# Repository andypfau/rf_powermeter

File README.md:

RF Powermeter
=============

A 10 MHz to 8 GHz RF power meter with USB connectivity.

## Design

## Photos

## Project Status

The hardware is working. The firmware is considered beta, but all functionality is implemented, and should work.

### Thoughts on Design

- The SMA connector is quite cheap, and will probably not last long (no stainless steel). Also, with the current design, the SMA tighening torque might break the solder connectio to the PCB (happened during testing).
- The HMC602 is EOL (see production notes below).

## Further Reading

- [RF Design](./doc/rfdesign.md)
- [Design Tools](./doc/designtools.md)
- [Production](./doc/production.md)
- [Serial Interface](./doc/serial.md)
- [Measurements](./doc/measurements.md)
- [Hardware Revisions](./doc/hwrev.md)

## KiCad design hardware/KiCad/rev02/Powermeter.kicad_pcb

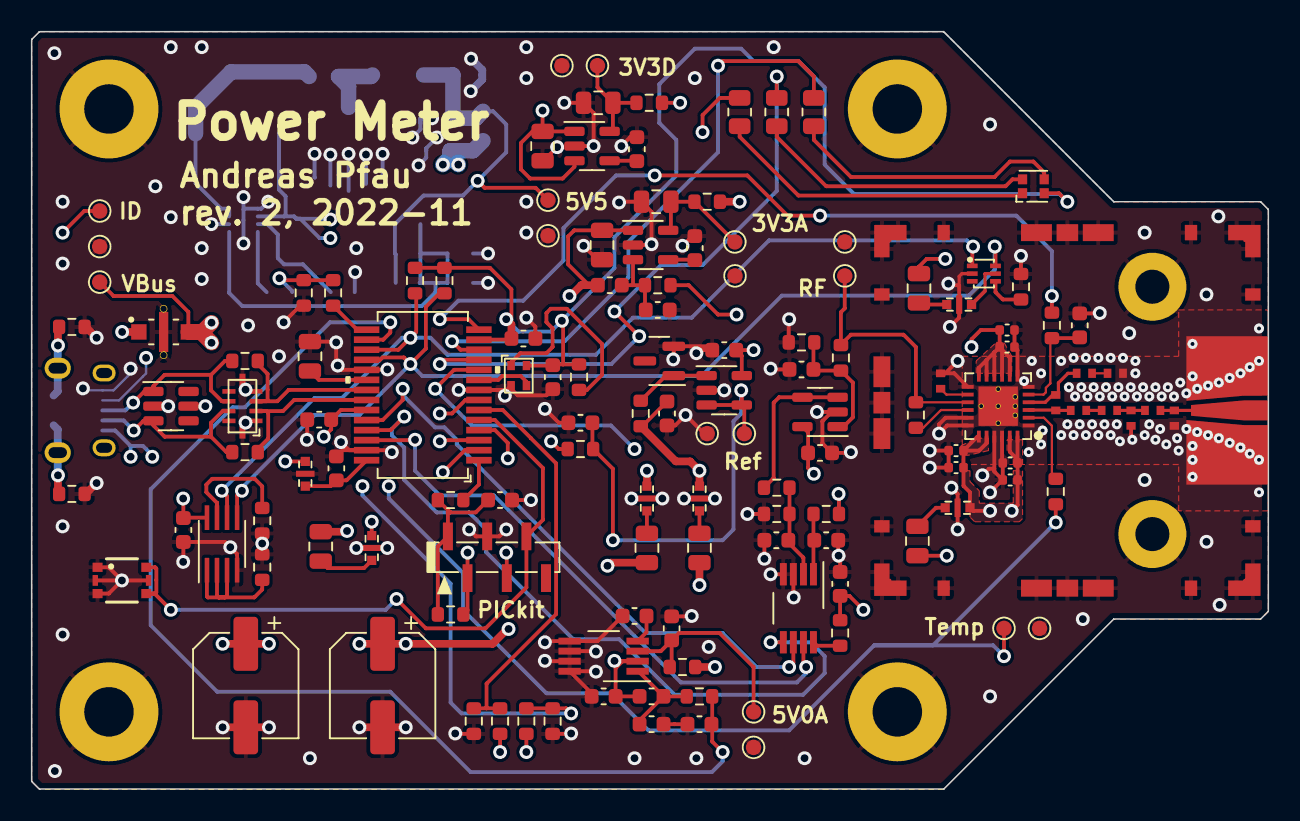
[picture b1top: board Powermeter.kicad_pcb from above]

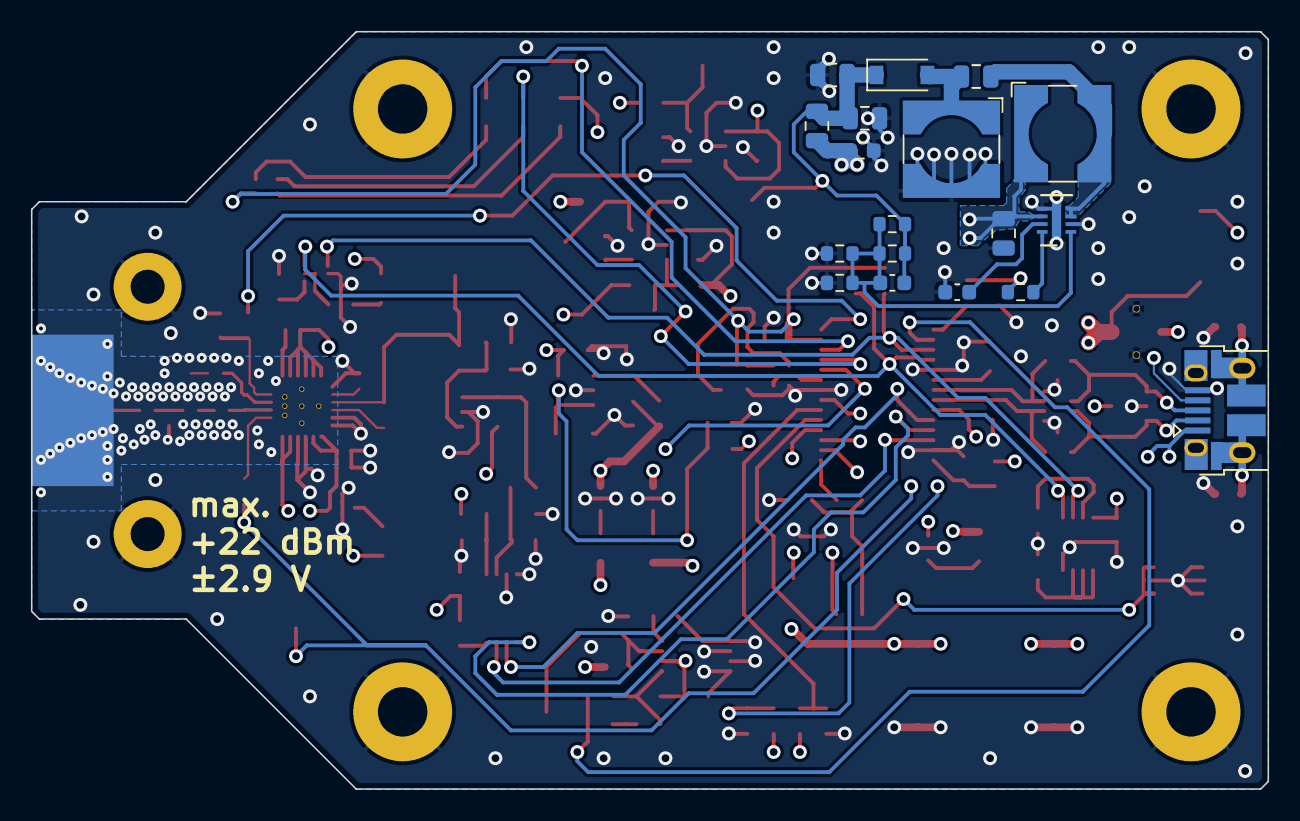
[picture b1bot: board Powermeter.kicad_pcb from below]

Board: 4 copper layers, 80.0 x 49.0 mm, 162 parts (18 on the bottom side), 84 nets.

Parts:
C301, C304, C306, C307, C308, C309, C402, C404, C410, C413, C602, C604, C605, C608, C609: C_100n_25V_Z5U_0603_small; C_0603_1608Metric
C302, C305, C501, C502, C601, C606: C_FT_100n_16V_0603; C_Feedthru_0603
C303, C416, C418: C_10n_50V_X7R_0603_small; C_0603_1608Metric
C310, C401, C411, C412, C417, C419: C_10µ_25V_X7R_0805; C_0805_2012Metric
C403: C_47n_50V_Z5U_0603_small; C_0603_1608Metric
C405, C407: C_Al_330µ_16V_UUD1C330MCL1GS; CP_Elec_6.3x5.8
C406, C414, C415: C_1µ_25V_X7R_0805; C_0805_2012Metric
C408: C_10n_50V_Z5U_0603_small; C_0603_1608Metric
C409: C_3p3_50V_NP0_0603_small; C_0603_1608Metric
C420, C421, C512: C_1n_50V_X7R_0603_small; C_0603_1608Metric
C503, C504: C_330p_50V_NP0_0402_small; R_0402_RF_Thru
C505, C506, C507: C_100n_10V_X7R_0402_small; C_0402_1005Metric
C508: C_220p_50V_NP0_0402_small; R_0402_RF_ToGND
C509, C510, C511: C_100p_50V_NP0_0402_small; C_0402_1005Metric
C603: C_22n_50V_X7R_0603_small; C_0603_1608Metric
C607: DNP; C_0603_1608Metric
D301: LED_RGB_EAST1616RGBB6; EAST1616RGBB6
D401: MBR0520L; D_SOD-123
D501: TPD1E0B04DPYT_TVS_0402; R_0402_RF_ToGND
FB301, FB401, FB501, FB502, FB601, FB602: FB_200mA_742792093; C_0805_2012Metric
FL201: NFE31PT221D1E9L_Filter; NFE31PT221D1E9L
J201: USB_B_Micro_Amphenol_10103594; USB_Micro-B_Amphenol_10103594-0001LF_Horizontal
J301: Conn_PICkit_1.27mm
J501: SMA-f_Molex732511150; Molex_SMA_732511150_Handsolder
L401, L402: WE744053100_PowerInd; L_Wuerth_WE-TPC-6.3mm
R201, R204, R301, R305, R306, R401, R402, R408, R409, R411, R412, R501, R508, R604: R_0_1P_thick_0603_small; R_0603_1608Metric
R202, R203, R407, R602, R605: DNP; R_0603_1608Metric
R302: R_10k_1P_thick_0603_small; R_0603_1608Metric
R303, R606, R607: R_10_1P_thick_0603_small; R_0603_1608Metric
R304, R308: R_100_1P_thick_0603_small; R_0603_1608Metric
R307: R_100k_1P_thick_0603_small; R_0603_1608Metric
R309, R310, R405: R_12k_1P_thick_0603_small; R_0603_1608Metric
R311: R_330_1P_thick_0805_small; R_0805_2012Metric
R312: R_270_1P_thick_0805_small; R_0805_2012Metric
R313: R_150_1P_thick_0805_small; R_0805_2012Metric
R314, R316, R507, R509: R_1k_1P_thick_0603_small; R_0603_1608Metric
R315, R317: R_1k1_1P_thick_0603_small; R_0603_1608Metric
R403, R410: DNP; C_0603_1608Metric
R404: R_68k_1P_thick_0603_small; R_0603_1608Metric
R406: R_110k_1P_thick_0603_small; R_0603_1608Metric
R502: 15; R_0402_RF_Thru
R503: 68; R_0402_RF_ToGND
R504: 27.4; R_0402_RF_Thru
R505: 49.9; R_0402_RF_ToGND
R506: 180; R_0402_RF_Thru
R601: R_68_1P_thick_0603_small; R_0603_1608Metric
R603: R_2k7_1P_thick_0603_small; R_0603_1608Metric
SW301: WE435151014824_PushBtn; WE435151014824
TP201, TP401, TP402, TP403, TP404, TP405, TP406, TP407, TP408, TP409, TP410, TP501, TP502, TP503, TP504, TP601, TP602: TestPoint; TestPoint_Pad_D1.0mm
U201: USBLC6-4; SOT-23-6
U202: EZA-DLU02AAJ; EZA-DLU
U301: Osc_8M_830208214709; Osc_IQD_2.0x1.6mm
U302: Memory_24CS512T-E-MS; SSOP-8_2.95x2.8mm_P0.65mm
U303: PIC24FJ32GU202-I-SS
U401: LT3467A; DFN-8-1EP_2x3mm_P0.5mm_EP0.61x2.2mm
U402: REG113EA-5; VSSOP-8_3.0x3.0mm_P0.65mm
U403, U404: LP2985IM5-3.3; SOT-23-5
U501: TMP112AQDRLRQ1; SOT-563_Smallpads
U502: HMC602LP4E_RF-Sensor; HMC602LP4
U601: LM4040BIM3-3.0; SOT-23
U602, U603: OP_MAX4230AUK+T; SOT-23-5
U604: ADS7822E-250; VSSOP-8_3.0x3.0mm_P0.65mm
X101, X102, X103, X104: MountingHoleConnected; MountingHole_3.2mm_M3_Pad
X105, X106: MountingHoleConnected; MountingHole_2.2mm_M2_Pad
X501, X503, X506, X508: CavityClip_Angled_S0981-46R; S0981-46R
X502, X504, X505: CavityClip_Straight_S0971-46R; S0971-46R

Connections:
+3V3A: FB601.1, R411.2
+3V3D: FB301.1, FB501.1, FB602.1, R412.2
+5V0A: FB502.1, R314.1, R408.2
+5V0USB: C401.1, C405.1, FL201.3, L401.1, R307.1, R308.2, R316.1, R401.1, TP403.1, U401.6 (V_{In})
+5V5: C404.1, C407.1, C413.1, C414.1, C415.1, FB401.2, R403.1, R410.1, U402.2 (V_{IN}), U403.1 (V_{IN}), U404.1 (V_{IN}), U404.3 (ON/~OFF)
/Converter/CS: U303.25 (CVREF/AN6/C3INB/RP14/RB14), U604.5 (~CS/SHDN)
/Converter/Clk: U303.26 (AN9/C3INA/RP15/RB15), U604.7 (DCLOCK)
/Converter/Local3V3A: C601.3, C602.1, C604.1, C605.1, R603.1, U602.5 (VDD), U603.5 (VDD)
/Converter/Local3V3D: C606.3, C609.1, R607.1
/Converter/Miso: U303.24 (AN7/C1INC/RP13/_RB13), U604.6 (D_{OUT})
/Converter/Ref3V0: C304.1, R303.1, R606.1, TP601.1, U603.3 (IN-), U603.4 (OUT)
/MCU/EnRf: R509.1, U303.14 (TMS/RP5/USBID/RB5)
/MCU/LedB: R313.1, U303.12 (SOSCO/SCLKI/C2INC/PWRLCLK/RA4)
/MCU/LedG: R312.1, U303.11 (SOSCI/C2IND/RP4/RB4)
/MCU/LedR: R311.1, U303.10 (OSCO/CLKO/C2IND/RA3)
/MCU/Osc: U301.3 (OUT), U303.9 (OSCI/CLKI/C1IND/RA2)
/MCU/PGC: J301.5 (PGC/ICSPCLK), SW301.2 (B), SW301.4 (B), U303.5 (PGEC1/AN1-/AN3/C2INA/RP1/RB1)
/MCU/PGD: J301.4 (PGD/ICSPDAT), U303.4 (PGED1/AN2/LVDIN/C2INB/RP0/RB0)
/MCU/S5V0A: R314.2, R315.1, U303.7 (AN5/C1INA/RP3/SCL2/RB3)
/MCU/S5V0USB: R316.2, R317.1, U303.6 (AN4/C1INB/RP2/SDA2/RB2)
/MCU/SCL: R310.2, U302.6 (SCL), U303.17 (TCK/RP8/SCL1/~USBOEN/RB8), U501.1 (SCL)
/MCU/SDA: R309.2, U302.5 (SDA), U303.18 (TDO/C1INC/C2INC/C3INC/RP9/SDA1/_T1CK/RB9), U501.6 (SDA)
/MCU/USBDM: R203.2, U202.3 (I/O1), U303.22 (PGEC2/RP11/D-/RB11)
/MCU/USBDP: R202.2, U202.4 (I/O2), U303.21 (PGED2/RP10/D+/RB10)
/MCU/VBUS: R308.1, U303.15 (VBUS/RB6)
/MCU/VCAP: C310.1, U303.20 (VCAP)
/MCU/VDD: C301.1, C302.3, C305.1, C306.1, C308.1, C309.1, D301.2 (A), J301.2 (VDD), R301.1, R302.1, R309.1, R310.1, U301.4 (V_{DD}), U302.8 (V_{CC}), U303.13 (VDD), U303.23 (VUSB3V3)
/MCU/VDDA: C305.3, C307.1, U303.28 (AVDD/VDD)
/RF/RF1: R502.2, R503.2, R504.1
/RF/RF2: C503.1, R504.2
/RF/RF3: C503.2, R506.2, U502.3 (INP)
/RF/RF4: C504.2, R506.1, U502.4 (INN)
/RF/RF5: C504.1, R505.1
/RF/RF_IN: D501.1 (A1), J501.1 (In), R502.1
/RF/RfSens: R508.2, R601.1, TP503.1, U502.15 (LOGOUT)
/RF/SensVcc: C502.3, C505.1, C506.1, C507.1, C509.1, C510.1, C511.1, U502.8 (VCC1), U502.9 (VCC1), U502.10 (VCC1), U502.11 (VCC1), U502.12 (VCC1), U502.19 (VCC2), U502.20 (VCC2), U502.23 (VCC3), U502.24 (VCC3)
/RF/TempSens: R507.2, TP501.1, U303.3 (PGEC3/CVREF-/AN1/C3IND/RP27/ASCL1/RA1)
/Supply/En: C402.1, R402.1, R409.1, U303.16 (TDI/RP7/INT0/RB7)
/USB/USBDM_UF: J201.3 (D+), R202.1, U201.1 (I/O1), U202.8 (I/O4)
/USB/USBDP_UF: J201.2 (D-), R203.1, U201.3 (I/O2), U202.9 (I/O3)
GND: C301.2, C302.2, C303.2, C304.2, C305.2, C306.2, C307.2, C308.2, C309.2, C310.2, C401.2, C402.2, C403.2, C404.2, C405.2, C407.2, C408.2, C410.2, C411.2, C412.2, C413.2, C414.2, C415.2, C416.2, C417.2, C418.2, C419.2, C420.2, C421.2, C501.2, C502.2, C505.2, C506.2, C507.2, C508.2, C509.2, C510.2, C511.2, C512.2, C601.2, C602.2, C603.2, C604.2, C605.2, C606.2, C607.2, C608.2, C609.2, D501.2 (A2), FL201.2, J201.5 (GND), J301.3 (VSS), J501.2 (Ext), L402.2, R201.2, R204.2, R305.2, R306.2, R307.2, R315.2, R317.2, R405.2, R407.2, R501.2, R503.1, R505.2, R602.2, R605.2, SW301.1 (A), SW301.3 (A), SW301.5 (GND), SW301.6 (GND), TP401.1, TP402.1, TP404.1, TP407.1, TP409.1, TP502.1, TP504.1, TP602.1, U201.2 (GND), U202.1 (GND), U202.2 (GND), U202.5 (GND), U202.6 (GND), U301.2 (GND), U302.4 (V_{SS}), U303.8 (VSS), U303.19 (VSS), U303.27 (AVSS/VSS), U401.2 (GND), U401.5 (GND), U401.9 (GND), U402.5 (GND), U402.6 (GND), U402.7 (GND), U402.8 (GND), U403.2 (GND), U404.2 (GND), U501.2 (GND), U502.1 (NC), U502.6 (NC), U502.7 (NC), U502.13 (NC), U502.17 (NC), U502.18 (NC), U502.21 (NC), U502.22 (NC), U502.25 (GND), U601.2 (-), U602.2 (VSS), U603.2 (VSS), U604.3 (-In), U604.4 (GND), X101.1, X102.1, X103.1, X104.1, X105.1, X106.1, X501.1 (e), X502.1 (e), X503.1 (e), X504.1 (e), X505.1 (e), X506.1 (e), X508.1 (e)
unnamed: C302.1, FB301.2
unnamed: C303.1, J301.1 (~MCLR/VPP), R302.2, R304.1
unnamed: C403.1, U401.7 (SS)
unnamed: C406.1, L401.2, U401.3 (SW), U401.4 (SW)
unnamed: C406.2, D401.2 (A), L402.1
unnamed: C408.1, U402.4 (NR)
unnamed: C409.1, C411.1, C412.1, D401.1 (K), FB401.1, R404.1, R406.1, TP405.1
unnamed: C409.2, R404.2, R405.1, R406.2, R407.1, U401.1 (FB)
unnamed: C410.1, R408.1, TP406.1, U402.3 (V_{OUT})
unnamed: C416.1, U403.4 (BP)
unnamed: C417.1, R411.1, TP408.1, U403.5 (V_{OUT})
unnamed: C418.1, U404.4 (BP)
unnamed: C419.1, R412.1, TP410.1, U404.5 (V_{OUT})
unnamed: C420.1, R402.2, R403.2, U402.1 (En)
unnamed: C421.1, R409.2, R410.2, U403.3 (ON/~OFF)
unnamed: C501.1, FB501.2
unnamed: C501.3, U501.5 (V+)
unnamed: C502.1, FB502.2
unnamed: C508.1, U502.14 (C_{LPF})
unnamed: C512.1, R509.2, U502.5 (EN)
unnamed: C601.1, FB601.2
unnamed: C603.1, R601.2, R602.1, U602.1 (IN+)
unnamed: C606.1, FB602.2
unnamed: C607.1, R604.2, R605.1, U604.2 (+In)
unnamed: C608.1, R606.2, U604.1 (V_{REF})
unnamed: D301.1 (RK), R311.2
unnamed: D301.3 (GK), R312.2
unnamed: D301.4 (BK), R313.2
unnamed: FL201.1, J201.1 (V_{BUS}), U201.5 (VBUS)
unnamed: J201.4 (ID), TP201.1
unnamed: J201.6 (Shield), R201.1, R204.1
unnamed: R301.2, U301.1 (En)
unnamed: R303.2, U303.2 (PGED3/VREF+/CVREF+/AN0/C3INC/RP26/ASDA1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)
unnamed: R304.2, U303.1 (~MCLR)
unnamed: R305.1, U302.1 (A0), U302.2 (A1), U302.3 (A2)
unnamed: R306.1, U302.7 (WP)
unnamed: R401.2, U401.8 (~SHDN)
unnamed: R501.1, U501.4 (ADD0)
unnamed: R507.1, U502.2 (TEMP)
unnamed: R508.1, U502.16 (V_{SET})
unnamed: R603.2, U601.1 (+), U603.1 (IN+)
unnamed: R604.1, U602.3 (IN-), U602.4 (OUT)
unnamed: R607.2, U604.8 (+V_{CC})

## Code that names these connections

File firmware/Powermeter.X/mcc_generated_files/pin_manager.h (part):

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*/
/**
  @Summary
    Sets the GPIO pin, RA1, high using LATA1.

  @Description
    Sets the GPIO pin, RA1, high using LATA1.

  @Preconditions
    The RA1 must be set to an output.
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#define Channel_RfTemp_SetHigh()          (_LATA1 = 1)
/**
  @Summary
    Sets the GPIO pin, RA1, low using LATA1.

  @Description
    Sets the GPIO pin, RA1, low using LATA1.

  @Preconditions
    The RA1 must be set to an output.
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#define Channel_RfTemp_SetLow()           (_LATA1 = 0)
/**
  @Summary
    Toggles the GPIO pin, RA1, using LATA1.

  @Description
    Toggles the GPIO pin, RA1, using LATA1.

  @Preconditions
    The RA1 must be set to an output.
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#define Channel_RfTemp_Toggle()           (_LATA1 ^= 1)
/**
  @Summary
    Reads the value of the GPIO pin, RA1.

  @Description
    Reads the value of the GPIO pin, RA1.

  @Preconditions
    None.
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    </code>

*/
#define Channel_RfTemp_GetValue()         _RA1
/**
  @Summary
    Configures the GPIO pin, RA1, as an input.

  @Description
    Configures the GPIO pin, RA1, as an input.

  @Preconditions
    None.
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#define Channel_RfTemp_SetDigitalInput()  (_TRISA1 = 1)
/**
  @Summary
    Configures the GPIO pin, RA1, as an output.

  @Description
    Configures the GPIO pin, RA1, as an output.

  @Preconditions
    None.
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#define Channel_RfTemp_SetDigitalOutput() (_TRISA1 = 0)
/**
  @Summary
    Sets the GPIO pin, RA3, high using LATA3.

  @Description
    Sets the GPIO pin, RA3, high using LATA3.

  @Preconditions
    The RA3 must be set to an output.
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#define IO_LedR_SetHigh()          (_LATA3 = 1)
/**
  @Summary
    Sets the GPIO pin, RA3, low using LATA3.

  @Description
    Sets the GPIO pin, RA3, low using LATA3.

  @Preconditions
    The RA3 must be set to an output.
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#define IO_LedR_SetLow()           (_LATA3 = 0)
/**
  @Summary
    Toggles the GPIO pin, RA3, using LATA3.

  @Description
    Toggles the GPIO pin, RA3, using LATA3.

  @Preconditions
    The RA3 must be set to an output.
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#define IO_LedR_Toggle()           (_LATA3 ^= 1)
/**
  @Summary
    Reads the value of the GPIO pin, RA3.

  @Description
    Reads the value of the GPIO pin, RA3.

  @Preconditions
    None.
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    </code>

*/
#define IO_LedR_GetValue()         _RA3
/**
  @Summary
    Configures the GPIO pin, RA3, as an input.

  @Description
    Configures the GPIO pin, RA3, as an input.

  @Preconditions
    None.
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#define IO_LedR_SetDigitalInput()  (_TRISA3 = 1)
/**
  @Summary
    Configures the GPIO pin, RA3, as an output.

  @Description
    Configures the GPIO pin, RA3, as an output.

  @Preconditions
    None.
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#define IO_LedR_SetDigitalOutput() (_TRISA3 = 0)
/**
  @Summary
    Sets the GPIO pin, RA4, high using LATA4.

  @Description
    Sets the GPIO pin, RA4, high using LATA4.

  @Preconditions
    The RA4 must be set to an output.
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#define IO_LedB_SetHigh()          (_LATA4 = 1)
/**
  @Summary
    Sets the GPIO pin, RA4, low using LATA4.

  @Description
    Sets the GPIO pin, RA4, low using LATA4.

  @Preconditions
    The RA4 must be set to an output.
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#define IO_LedB_SetLow()           (_LATA4 = 0)
/**
  @Summary
    Toggles the GPIO pin, RA4, using LATA4.

  @Description
    Toggles the GPIO pin, RA4, using LATA4.

  @Preconditions
    The RA4 must be set to an output.
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#define IO_LedB_Toggle()           (_LATA4 ^= 1)
/**
  @Summary
    Reads the value of the GPIO pin, RA4.

  @Description
    Reads the value of the GPIO pin, RA4.

  @Preconditions
    None.
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    </code>

*/
#define IO_LedB_GetValue()         _RA4
/**
  @Summary
    Configures the GPIO pin, RA4, as an input.

  @Description
    Configures the GPIO pin, RA4, as an input.

  @Preconditions
    None.
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#define IO_LedB_SetDigitalInput()  (_TRISA4 = 1)
/**
  @Summary
    Configures the GPIO pin, RA4, as an output.

  @Description
    Configures the GPIO pin, RA4, as an output.

  @Preconditions
    None.
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#define IO_LedB_SetDigitalOutput() (_TRISA4 = 0)
/**
  @Summary
    Sets the GPIO pin, RB0, high using LATB0.

  @Description
    Sets the GPIO pin, RB0, high using LATB0.

  @Preconditions
    The RB0 must be set to an output.
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#define IO_RB0_SetHigh()          (_LATB0 = 1)
/**
  @Summary
    Sets the GPIO pin, RB0, low using LATB0.

  @Description
    Sets the GPIO pin, RB0, low using LATB0.

  @Preconditions
    The RB0 must be set to an output.
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#define IO_RB0_SetLow()           (_LATB0 = 0)
/**
  @Summary
    Toggles the GPIO pin, RB0, using LATB0.

  @Description
    Toggles the GPIO pin, RB0, using LATB0.

  @Preconditions
    The RB0 must be set to an output.
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#define IO_RB0_Toggle()           (_LATB0 ^= 1)
/**
  @Summary
    Reads the value of the GPIO pin, RB0.

  @Description
    Reads the value of the GPIO pin, RB0.

  @Preconditions
    None.
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    </code>

*/
#define IO_RB0_GetValue()         _RB0
/**
  @Summary
    Configures the GPIO pin, RB0, as an input.

  @Description
    Configures the GPIO pin, RB0, as an input.

  @Preconditions
    None.
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#define IO_RB0_SetDigitalInput()  (_TRISB0 = 1)
/**
  @Summary
    Configures the GPIO pin, RB0, as an output.

  @Description
    Configures the GPIO pin, RB0, as an output.

  @Preconditions
    None.
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#define IO_RB0_SetDigitalOutput() (_TRISB0 = 0)
/**
  @Summary
    Sets the GPIO pin, RB1, high using LATB1.

  @Description
    Sets the GPIO pin, RB1, high using LATB1.

  @Preconditions
    The RB1 must be set to an output.
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#define IO_Button_SetHigh()          (_LATB1 = 1)
/**
  @Summary
    Sets the GPIO pin, RB1, low using LATB1.

  @Description
    Sets the GPIO pin, RB1, low using LATB1.

  @Preconditions
    The RB1 must be set to an output.
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#define IO_Button_SetLow()           (_LATB1 = 0)
/**
  @Summary
    Toggles the GPIO pin, RB1, using LATB1.

  @Description
    Toggles the GPIO pin, RB1, using LATB1.

  @Preconditions
    The RB1 must be set to an output.
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#define IO_Button_Toggle()           (_LATB1 ^= 1)
/**
  @Summary
    Reads the value of the GPIO pin, RB1.

  @Description
    Reads the value of the GPIO pin, RB1.

  @Preconditions
    None.
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    </code>

*/
#define IO_Button_GetValue()         _RB1
/**
  @Summary
    Configures the GPIO pin, RB1, as an input.

  @Description
    Configures the GPIO pin, RB1, as an input.

  @Preconditions
    None.
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#define IO_Button_SetDigitalInput()  (_TRISB1 = 1)
/**
  @Summary
    Configures the GPIO pin, RB1, as an output.

  @Description
    Configures the GPIO pin, RB1, as an output.

  @Preconditions
    None.
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#define SPI_SDI_SetDigitalOutput() (_TRISB13 = 0)
/**
  @Summary
    Sets the GPIO pin, RB14, high using LATB14.

  @Description
    Sets the GPIO pin, RB14, high using LATB14.

  @Preconditions
    The RB14 must be set to an output.
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#define SPI_CSD_SetHigh()          (_LATB14 = 1)
/**
  @Summary
    Sets the GPIO pin, RB14, low using LATB14.

  @Description
    Sets the GPIO pin, RB14, low using LATB14.

  @Preconditions
    The RB14 must be set to an output.
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#define SPI_CSD_SetLow()           (_LATB14 = 0)
/**
  @Summary
    Toggles the GPIO pin, RB14, using LATB14.

  @Description
    Toggles the GPIO pin, RB14, using LATB14.

  @Preconditions
    The RB14 must be set to an output.
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#define SPI_CSD_Toggle()           (_LATB14 ^= 1)
/**
  @Summary
    Reads the value of the GPIO pin, RB14.

  @Description
    Reads the value of the GPIO pin, RB14.

  @Preconditions
    None.
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    </code>

*/
#define SPI_CSD_GetValue()         _RB14
/**
  @Summary
    Configures the GPIO pin, RB14, as an input.

  @Description
    Configures the GPIO pin, RB14, as an input.

  @Preconditions
    None.
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#define SPI_CSD_SetDigitalInput()  (_TRISB14 = 1)
/**
  @Summary
    Configures the GPIO pin, RB14, as an output.

  @Description
    Configures the GPIO pin, RB14, as an output.

  @Preconditions
    None.
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#define SPI_CSD_SetDigitalOutput() (_TRISB14 = 0)
/**
  @Summary
    Sets the GPIO pin, RB15, high using LATB15.

  @Description
    Sets the GPIO pin, RB15, high using LATB15.

  @Preconditions
    The RB15 must be set to an output.
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#define SPI_CLK_SetHigh()          (_LATB15 = 1)
/**
  @Summary
    Sets the GPIO pin, RB15, low using LATB15.

  @Description
    Sets the GPIO pin, RB15, low using LATB15.

  @Preconditions
    The RB15 must be set to an output.
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#define SPI_CLK_SetLow()           (_LATB15 = 0)
/**
  @Summary
    Toggles the GPIO pin, RB15, using LATB15.

  @Description
    Toggles the GPIO pin, RB15, using LATB15.

  @Preconditions
    The RB15 must be set to an output.
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#define SPI_CLK_Toggle()           (_LATB15 ^= 1)
/**
  @Summary
    Reads the value of the GPIO pin, RB15.

  @Description
    Reads the value of the GPIO pin, RB15.

  @Preconditions
    None.
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    </code>

*/
#define SPI_CLK_GetValue()         _RB15
/**
  @Summary
    Configures the GPIO pin, RB15, as an input.

  @Description
    Configures the GPIO pin, RB15, as an input.

  @Preconditions
    None.
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#define SPI_CLK_SetDigitalInput()  (_TRISB15 = 1)
/**
  @Summary
    Configures the GPIO pin, RB15, as an output.

  @Description
    Configures the GPIO pin, RB15, as an output.

  @Preconditions
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
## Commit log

2022-12-10 Some cleanup
2022-12-18 Worked on doc
2022-12-18 Worked on firmware
2022-12-18 Worked on cal data; not working yet
2022-12-20 Worked on cal
2022-12-22 Uploading cal data is working no
2022-12-23 Worked on cal; fixed an issue with endianness of data; fixed a rendering issue
2022-12-23 Cal s working now; updated docs
2022-12-23 Fixed EEPROM write timing; updated doc
2022-12-29 Some FW tweaks and fixes
2022-12-30 Changed default frequency; changed build to release

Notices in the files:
firmware/Powermeter.X/mcc_generated_files/pin_manager.h:
(c) 2020 Microchip Technology Inc. and its subsidiaries. You may use this
parts and their libraries:
Copyright 2021 Accelerated Designs. All rights reserved.
